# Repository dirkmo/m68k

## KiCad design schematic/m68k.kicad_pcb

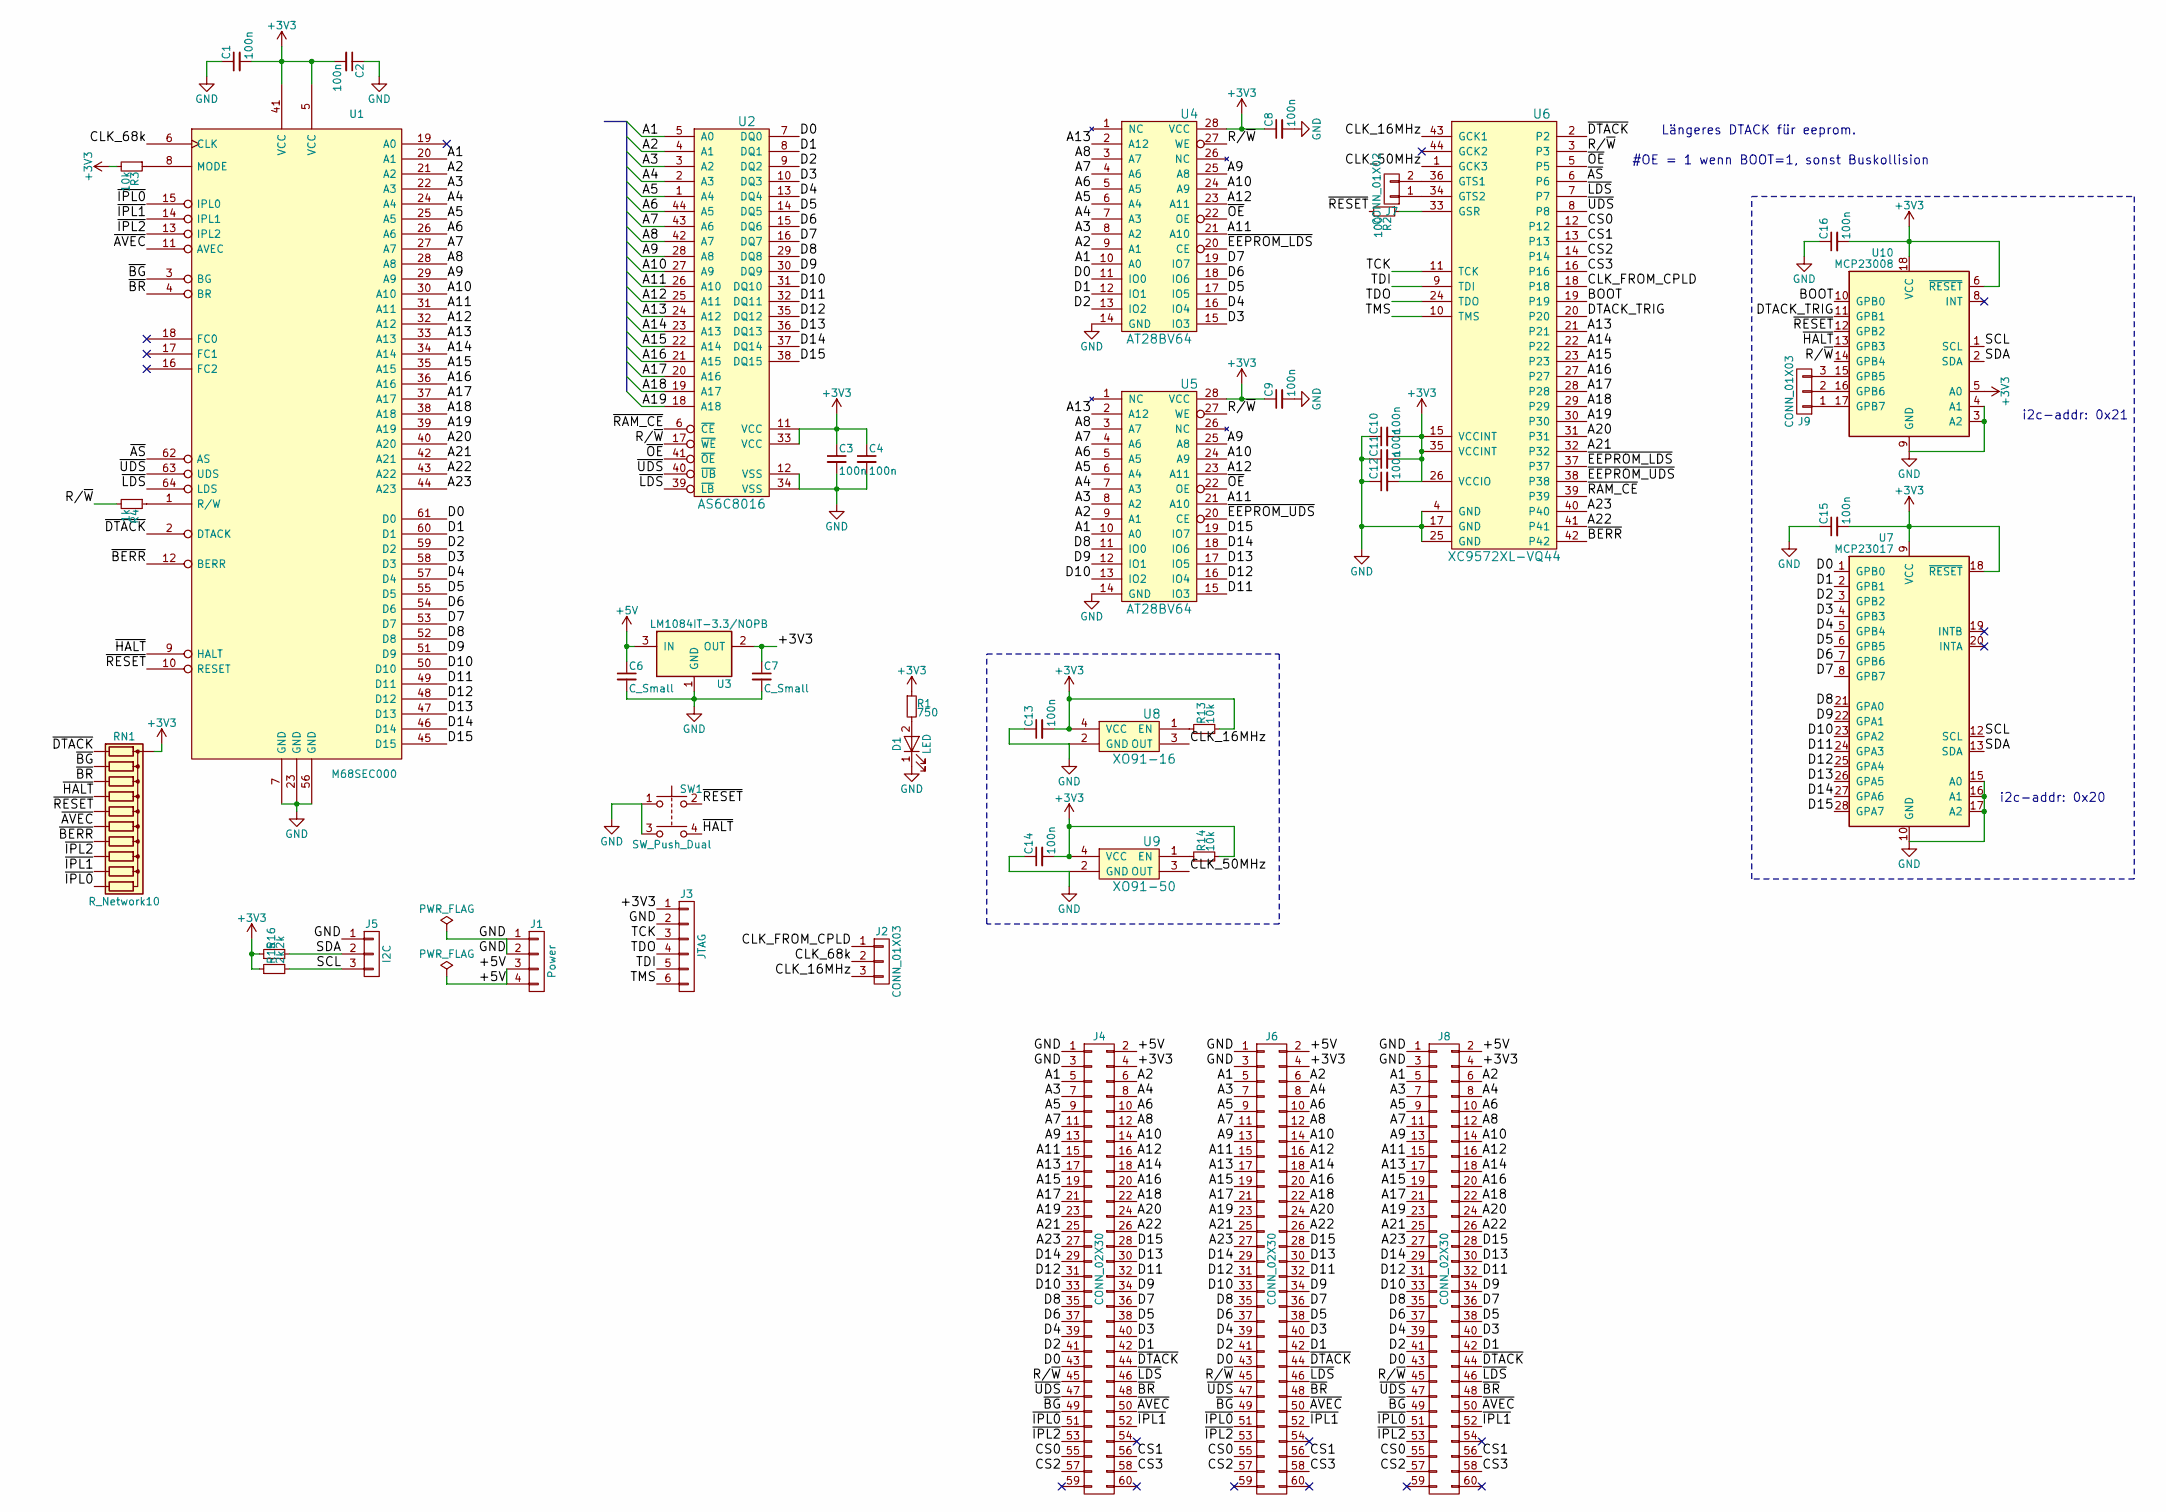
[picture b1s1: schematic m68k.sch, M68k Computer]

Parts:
C1, C2, C3, C4, C8, C9, C10, C11, C12, C13, C14, C15, C16: 100n; C_0805_HandSoldering
C6, C7: C_Small; C_0805_HandSoldering
D1: LED; LED_0805
J1: Power; Pin_Header_Straight_1x04_Pitch2.54mm
J2, J9: CONN_01X03; Pin_Header_Straight_1x03_Pitch2.54mm
J3: JTAG; Pin_Header_Straight_1x06_Pitch2.54mm
J4, J6, J8: CONN_02X30; IDC_Header_Straight_60pins
J5: I2C; Pin_Header_Straight_1x03_Pitch2.54mm
J7: CONN_01X02; Pin_Header_Straight_1x02_Pitch2.54mm
R1: 750; R_0805_HandSoldering
R2: 100; R_0805_HandSoldering
R3, R13, R14: 10k; R_0805_HandSoldering
R4: 1k; R_0805_HandSoldering
R15, R16: 2k; R_0805_HandSoldering
RN1: R_Network10; R_Array_SIP11
SW1: SW_Push_Dual; SW_TH_Tactile_Omron_B3F-10xx
U1: M68SEC000; TQFP-64_14x14mm_Pitch0.8mm
U2: AS6C8016; TSOP44
U3: LM1084IT-3.3/NOPB; TO-220_Horizontal
U4, U5: AT28BV64; SOIC-28W_7.5x17.9mm_Pitch1.27mm
U6: XC9572XL-VQ44; TQFP-44_10x10mm_Pitch0.8mm
U7: MCP23017; SOIC-28W_7.5x17.9mm_Pitch1.27mm
U8: XO91-16; Crystal_SMD_EuroQuartz_MQ-4pin_7.0x5.0mm_HandSoldering
U9: XO91-50; Crystal_SMD_EuroQuartz_MQ-4pin_7.0x5.0mm_HandSoldering
U10: MCP23008; SOIC-18W_7.5x11.6mm_Pitch1.27mm

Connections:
+3V3: C1.2, C2.2, C3.1, C4.1, C7.1, C8.1, C9.1, C10.2, C11.2, C12.2, C13.2, C14.2, C15.2, C16.2, J3.1, J4.4, J6.4, J8.4, R1.1, R3.2, R13.2, R14.2, R15.1, R16.1, RN1.1 (common), U1.5 (VCC), U1.41 (VCC), U2.11 (VCC), U2.33 (VCC), U3.2 (OUT), U4.28 (VCC), U5.28 (VCC), U6.15 (VCCINT), U6.26 (VCCIO), U6.35 (VCCINT), U7.9 (VCC), U7.18 (~RESET), U8.4 (VCC), U9.4 (VCC), U10.5 (A0), U10.6 (~RESET), U10.18 (VCC)
/A1: J4.5, J6.5, J8.5, U1.20 (A1), U2.5 (A0), U4.10 (A0), U5.10 (A0)
/A2: J4.6, J6.6, J8.6, U1.21 (A2), U2.4 (A1), U4.9 (A1), U5.9 (A1)
/A3: J4.7, J6.7, J8.7, U1.22 (A3), U2.3 (A2), U4.8 (A2), U5.8 (A2)
/A4: J4.8, J6.8, J8.8, U1.24 (A4), U2.2 (A3), U4.7 (A3), U5.7 (A3)
/A5: J4.9, J6.9, J8.9, U1.25 (A5), U2.1 (A4), U4.6 (A4), U5.6 (A4)
/A6: J4.10, J6.10, J8.10, U1.26 (A6), U2.44 (A5), U4.5 (A5), U5.5 (A5)
/A7: J4.11, J6.11, J8.11, U1.27 (A7), U2.43 (A6), U4.4 (A6), U5.4 (A6)
/A8: J4.12, J6.12, J8.12, U1.28 (A8), U2.42 (A7), U4.3 (A7), U5.3 (A7)
/A9: J4.13, J6.13, J8.13, U1.29 (A9), U2.28 (A8), U4.25 (A8), U5.25 (A8)
/A10: J4.14, J6.14, J8.14, U1.30 (A10), U2.27 (A9), U4.24 (A9), U5.24 (A9)
/A11: J4.15, J6.15, J8.15, U1.31 (A11), U2.26 (A10), U4.21 (A10), U5.21 (A10)
/A12: J4.16, J6.16, J8.16, U1.32 (A12), U2.25 (A11), U4.23 (A11), U5.23 (A11)
/A13: J4.17, J6.17, J8.17, U1.33 (A13), U2.24 (A12), U4.2 (A12), U5.2 (A12), U6.21
/A14: J4.18, J6.18, J8.18, U1.34 (A14), U2.23 (A13), U6.22
/A15: J4.19, J6.19, J8.19, U1.35 (A15), U2.22 (A14), U6.23
/A16: J4.20, J6.20, J8.20, U1.36 (A16), U2.21 (A15), U6.27
/A17: J4.21, J6.21, J8.21, U1.37 (A17), U2.20 (A16), U6.28
/A18: J4.22, J6.22, J8.22, U1.38 (A18), U2.19 (A17), U6.29
/A19: J4.23, J6.23, J8.23, U1.39 (A19), U2.18 (A18), U6.30
/A20: J4.24, J6.24, J8.24, U1.40 (A20), U6.31
/A21: J4.25, J6.25, J8.25, U1.42 (A21), U6.32
/A22: J4.26, J6.26, J8.26, U1.43 (A22), U6.41
/A23: J4.27, J6.27, J8.27, U1.44 (A23), U6.40
/BOOT: U6.19, U10.10 (GPB0)
/CLK_16MHz: J2.3, U6.43 (GCK1), U8.3 (OUT)
/CLK_50MHz: U6.1 (GCK3), U9.3 (OUT)
/CLK_68k: J2.2, U1.6 (CLK)
/CLK_FROM_CPLD: J2.1, U6.18
/CS0: J4.55, J6.55, J8.55, U6.12
/CS1: J4.56, J6.56, J8.56, U6.13
/CS2: J4.57, J6.57, J8.57, U6.14
/CS3: J4.58, J6.58, J8.58, U6.16
/D0: J4.43, J6.43, J8.43, U1.61 (D0), U2.7 (DQ0), U4.11 (IO0), U7.1 (GPB0)
/D1: J4.42, J6.42, J8.42, U1.60 (D1), U2.8 (DQ1), U4.12 (IO1), U7.2 (GPB1)
/D2: J4.41, J6.41, J8.41, U1.59 (D2), U2.9 (DQ2), U4.13 (IO2), U7.3 (GPB2)
/D3: J4.40, J6.40, J8.40, U1.58 (D3), U2.10 (DQ3), U4.15 (IO3), U7.4 (GPB3)
/D4: J4.39, J6.39, J8.39, U1.57 (D4), U2.13 (DQ4), U4.16 (IO4), U7.5 (GPB4)
/D5: J4.38, J6.38, J8.38, U1.55 (D5), U2.14 (DQ5), U4.17 (IO5), U7.6 (GPB5)
/D6: J4.37, J6.37, J8.37, U1.54 (D6), U2.15 (DQ6), U4.18 (IO6), U7.7 (GPB6)
/D7: J4.36, J6.36, J8.36, U1.53 (D7), U2.16 (DQ7), U4.19 (IO7), U7.8 (GPB7)
/D8: J4.35, J6.35, J8.35, U1.52 (D8), U2.29 (DQ8), U5.11 (IO0), U7.21 (GPA0)
/D9: J4.34, J6.34, J8.34, U1.51 (D9), U2.30 (DQ9), U5.12 (IO1), U7.22 (GPA1)
/D10: J4.33, J6.33, J8.33, U1.50 (D10), U2.31 (DQ10), U5.13 (IO2), U7.23 (GPA2)
/D11: J4.32, J6.32, J8.32, U1.49 (D11), U2.32 (DQ11), U5.15 (IO3), U7.24 (GPA3)
/D12: J4.31, J6.31, J8.31, U1.48 (D12), U2.35 (DQ12), U5.16 (IO4), U7.25 (GPA4)
/D13: J4.30, J6.30, J8.30, U1.47 (D13), U2.36 (DQ13), U5.17 (IO5), U7.26 (GPA5)
/D14: J4.29, J6.29, J8.29, U1.46 (D14), U2.37 (DQ14), U5.18 (IO6), U7.27 (GPA6)
/D15: J4.28, J6.28, J8.28, U1.45 (D15), U2.38 (DQ15), U5.19 (IO7), U7.28 (GPA7)
/DTACK_TRIG: U6.20, U10.11 (GPB1)
/R/~W: J4.45, J6.45, J8.45, R4.2, U2.17 (~WE), U4.27 (WE), U5.27 (WE), U6.3, U10.14 (GPB4)
/SCL: J5.3, R15.2, U7.12 (SCL), U10.1 (SCL)
/SDA: J5.2, R16.2, U7.13 (SDA), U10.2 (SDA)
/TCK: J3.3, U6.11 (TCK)
/TDI: J3.5, U6.9 (TDI)
/TDO: J3.4, U6.24 (TDO)
/TMS: J3.6, U6.10 (TMS)
/~AS: U1.62 (AS), U6.6
/~AVEC: J4.50, J6.50, J8.50, RN1.7 (R6), U1.11 (AVEC)
/~BERR: RN1.8 (R7), U1.12 (BERR), U6.42
/~BG: J4.49, J6.49, J8.49, RN1.3 (R2), U1.3 (BG)
/~BR: J4.48, J6.48, J8.48, RN1.4 (R3), U1.4 (BR)
/~DTACK: J4.44, J6.44, J8.44, RN1.2 (R1), U1.2 (DTACK), U6.2
/~EEPROM_LDS: U4.20 (CE), U6.37
/~EEPROM_UDS: U5.20 (CE), U6.38
/~HALT: RN1.5 (R4), SW1.4, U1.9 (HALT), U10.13 (GPB3)
/~IPL0: J4.51, J6.51, J8.51, RN1.11 (R10), U1.15 (IPL0)
/~IPL1: J4.52, J6.52, J8.52, RN1.10 (R9), U1.14 (IPL1)
/~IPL2: J4.53, J6.53, J8.53, RN1.9 (R8), U1.13 (IPL2)
/~LDS: J4.46, J6.46, J8.46, U1.64 (LDS), U2.39 (~LB), U6.7
/~OE: U2.41 (~OE), U4.22 (OE), U5.22 (OE), U6.5
/~RAM_CE: U2.6 (~CE), U6.39
/~RESET: R2.2, RN1.6 (R5), SW1.2, U1.10 (RESET), U10.12 (GPB2)
/~UDS: J4.47, J6.47, J8.47, U1.63 (UDS), U2.40 (~UB), U6.8
unnamed: D1.2 (A), R1.2
unnamed: J7.1, U6.34 (GTS2)
unnamed: J7.2, U6.36 (GTS1)
unnamed: J9.1, U10.17 (GPB7)
unnamed: J9.2, U10.16 (GPB6)
unnamed: J9.3, U10.15 (GPB5)
unnamed: R2.1, U6.33 (GSR)
unnamed: R3.1, U1.8 (MODE)
unnamed: R4.1, U1.1 (R/W)
unnamed: R13.1, U8.1 (EN)
unnamed: R14.1, U9.1 (EN)

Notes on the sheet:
#OE = 1 wenn BOOT=1, sonst Buskollision
i2c-addr: 0x20
i2c-addr: 0x21
Längeres DTACK für eeprom.

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
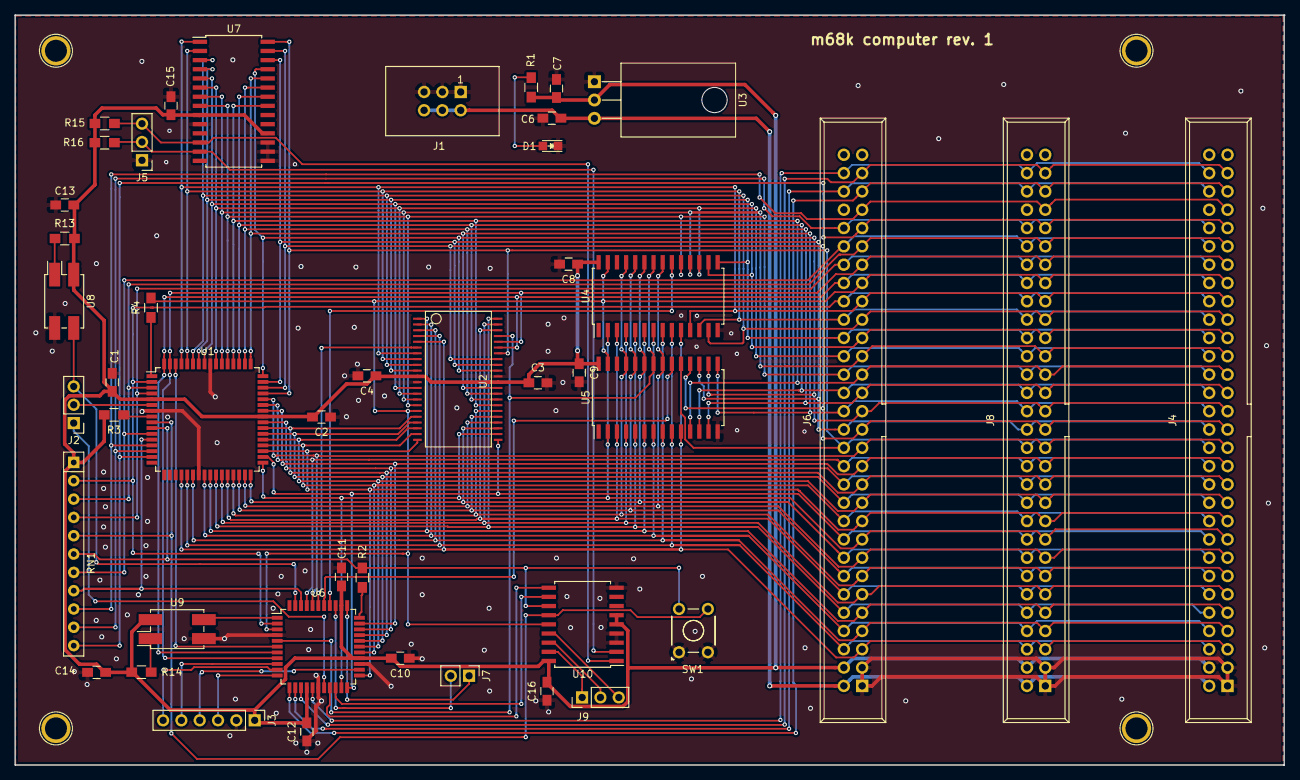
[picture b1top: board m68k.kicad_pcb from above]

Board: 2 copper layers, 176.1 x 104.0 mm, 45 parts (0 on the bottom side), 87 nets.

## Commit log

2017-08-04 initial import
2017-08-04 moved cpu to own sheet
2017-08-05 added sram symbol
2017-08-06 boot process
2017-08-06 moved all components onto top sheet
2017-08-07 added voltage regulator
2017-08-09 save
2017-08-09 further work
2017-08-10 docs and footprint
2017-08-12 further improvements
2017-08-12 moved files into subdirectory, added cpld file
2017-08-12 added gitignore file
2017-08-13 added cpld code, added LED
2017-08-14 - added halt_n and reset_n to 8-bit portexpander - implemented dtack state machine - some simple test benching
2017-08-15 hide eeprom when written to it. eeprom available after ram.
2017-08-16 fixed bug
2017-08-16 layout start
2017-08-17 - added Xilinx ISE project files - fixed two bugs in m68k.v
2017-08-17 layout work
2017-08-18 - further layout
2017-08-20 - changed pin assignment - further layout
2017-08-20 further layout
2017-08-20 layout pretty far
2017-08-21 no cs for external devices in boot mode
2017-08-21 layout done
2017-08-22 new design rules and fresh layout
2017-08-22 routing started
2017-08-23 weiter
2017-08-30 routing done
2017-09-02 corrected footprints
2017-09-03 mounting holes missing
2017-09-03 mounting holes added
2017-09-03 layout done again
2017-09-03 done.
2017-09-03 bootstrap program
2017-09-06 moved schematic into subfolder
2017-09-06 added extboard
2017-09-07 created ft232r symbol
2017-09-09 Entwurf extboard
2017-09-09 WIZ820 user manual
2017-09-10 - iack fehlt auf m68k - extboard mit dspic30f6014a - zusätzlich propeller für terminal
2017-09-13 srec parser
2017-09-24 import of bus pirate python code
2017-09-24 bus pirate
2017-10-01 added buspirate dlang code
2017-10-03 serial blah
2017-10-03 bp mode switching
2017-10-03 i2c send
2017-10-03 bootstrap.sh
2017-10-15 dserial als Modul zu bootstrap hinzugefügt.
2017-10-15 Portexpander-Klasse begonnen
2017-10-16 Port expander
2017-10-16 PortExpander Set/Get Register
2017-10-17 Port Expander Klasse fertig implementiert
2017-10-17 Standard-Devices für Linux/OSX
2017-10-17 uups
2017-10-19 reset.d
2017-10-20 properties für olat, iodir
2017-10-21 control und databus Klassen
2017-10-21 test
2018-01-29 bugfix register map portexpander
